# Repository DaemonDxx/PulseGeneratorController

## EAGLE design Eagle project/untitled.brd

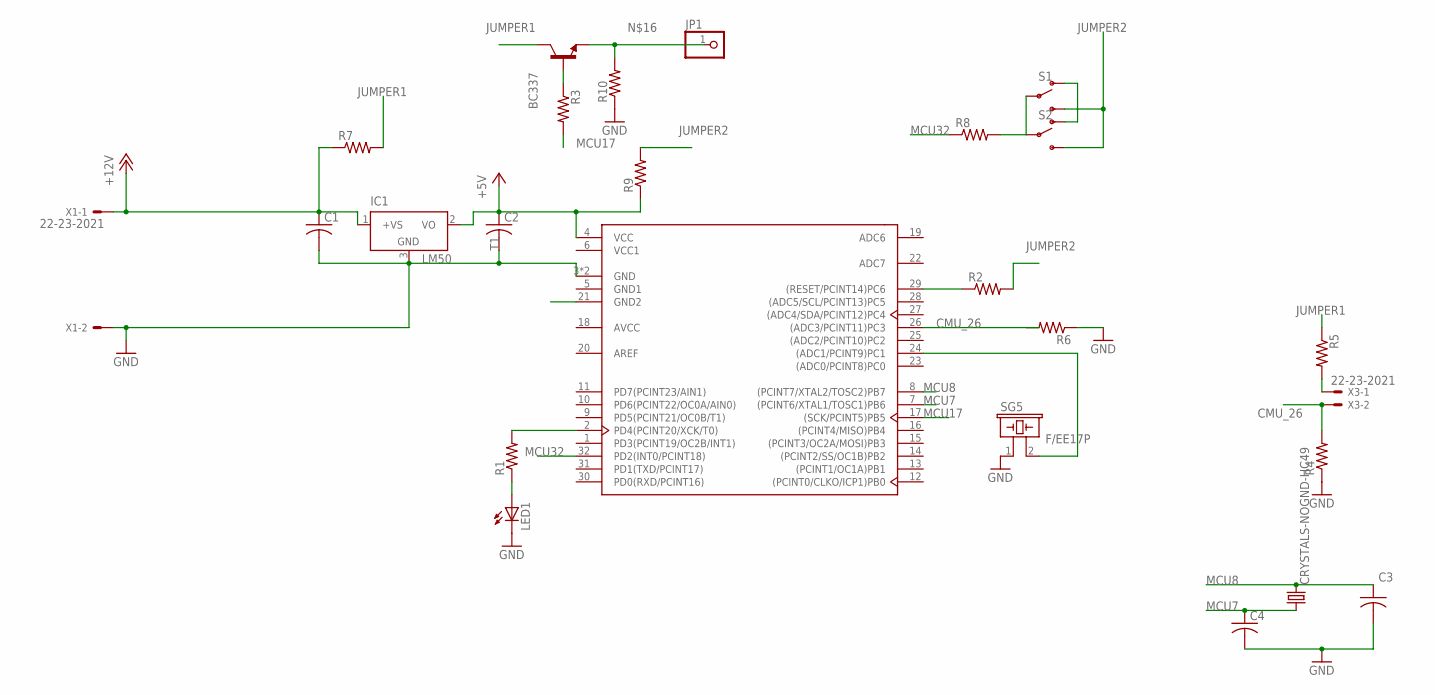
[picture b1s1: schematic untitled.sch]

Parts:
C1, C2: C-USC1206K; C1206K
C3, C4: C-USC0603K; C0603K
IC1: LM50; SOT23
JP1: PINHD-1X1; 1X01
LED1: LED3MM
R1, R3, R4, R5, R6, R7, R8, R9, R10: R-US_0204/7; 0204/7
R2: R-US_R0603; R0603
S1, S2: SWITCH-SPDT-PTH-11.6X4.0MM-LOCK; SWITCH_SPDT_PTH_11.6X4.0MM_LOCK
SG5: F/EE17P
T1: BC337; TO92
U1: ATMEGA328P-MU; VQFN-32
X1, X3: 22-23-2021
X2: CRYSTALS-NOGND-HC49; HC49

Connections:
+5V: C2.1, IC1.2 (VO), R9.1, U1.4 (VCC)
+12V: C1.1, IC1.1 (+VS), R7.1, X1.1
AREF: U1.20 (AREF)
AVCC: U1.18 (AVCC)
CMU_26: R4.2, R6.2, U1.26 ((ADC3/PCINT11)PC3), X3.2
GND: C1.2, C2.2, C3.2, C4.2, IC1.3 (GND), LED1.K (C), R4.1, R6.1, R10.1, SG5.1, U1.3 (GND), U1.33 (GND), X1.2
GND1: U1.5 (GND1)
JUMPER1: R5.1, R7.2, T1.3 (C)
JUMPER2: R2.2, R9.2, S1.3 (S), S2.3 (S)
MCU7: C4.1, U1.7 ((PCINT6/XTAL1/TOSC1)PB6), X2.1
MCU8: C3.1, U1.8 ((PCINT7/XTAL2/TOSC2)PB7), X2.2
MCU17: R3.2, U1.17 ((SCK/PCINT5)PB5)
MCU32: U1.32 (PD2(INT0/PCINT18))
unnamed: R1.2, U1.2 (PD4(PCINT20/XCK/T0))
unnamed: LED1.A, R1.1
unnamed: R2.1, U1.29 ((RESET/PCINT14)PC6)
unnamed: R3.1, T1.2 (B)
unnamed: R5.2, X3.1
unnamed: JP1.1, R10.2, T1.1 (E)
unnamed: SG5.2, U1.24 ((ADC1/PCINT9)PC1)
unnamed: R8.2, S1.2, S2.2
unnamed: S1.1 (O), S2.1 (O)
VCC1: U1.6 (VCC1)

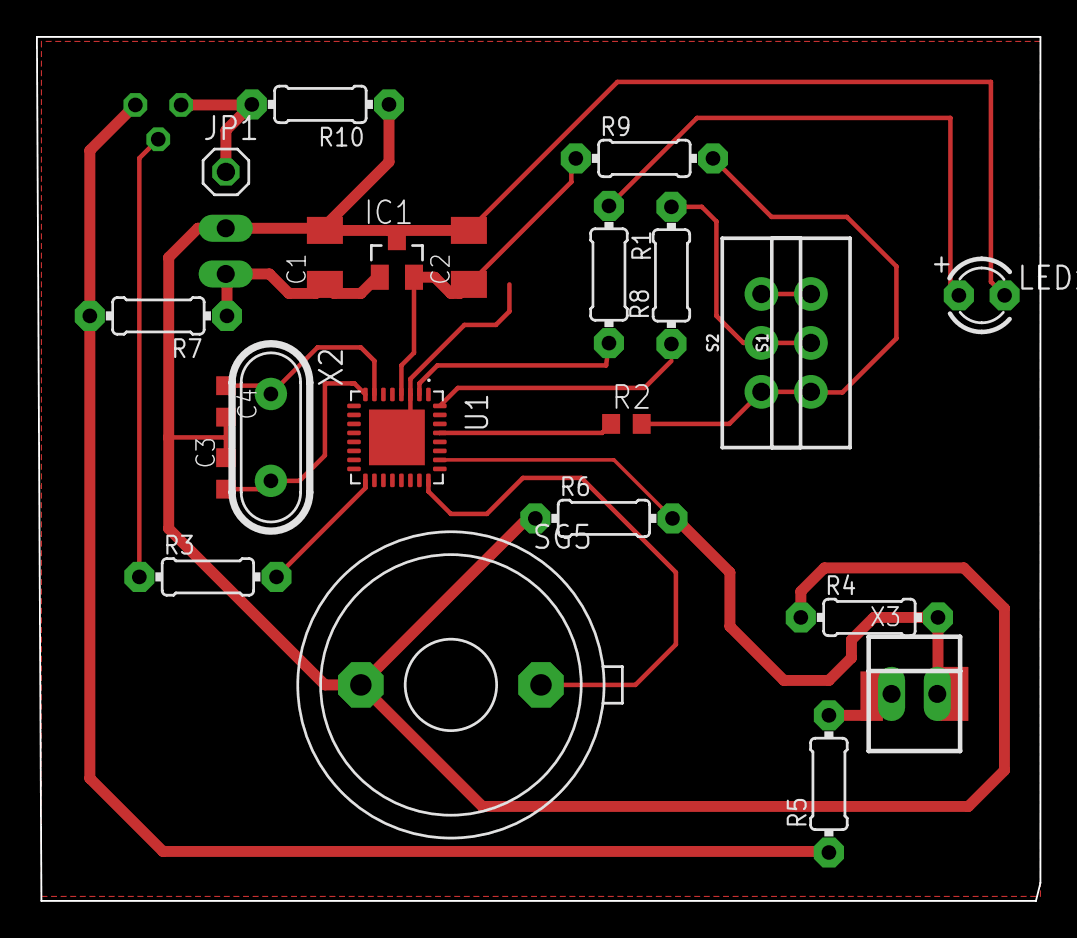
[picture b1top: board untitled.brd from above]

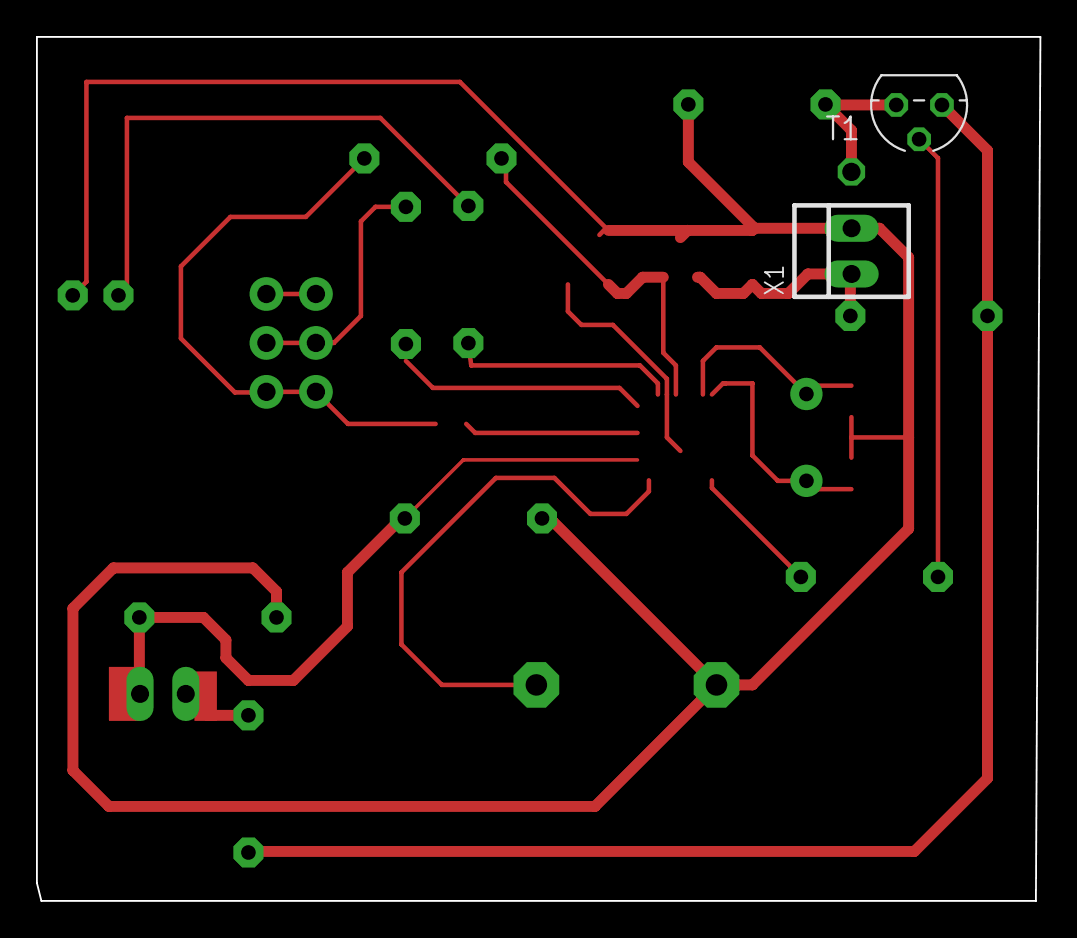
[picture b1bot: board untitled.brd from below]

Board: 2 copper layers, 55.8 x 48.0 mm, 25 parts (2 on the bottom side), 18 nets.

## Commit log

2020-06-25 Проект с печатной платой v1
    Добавлен проект Eagle с печатной платой

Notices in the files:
parts and their libraries:
SparkFun-Switches: Licensing: Creative Commons ShareAlike 4.0 International - https://creativecommons.org/licenses/by-sa/4.0
